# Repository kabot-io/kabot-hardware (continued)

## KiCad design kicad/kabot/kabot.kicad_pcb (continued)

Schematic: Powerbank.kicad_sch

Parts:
C1, C2, C7: 22u; C_1206_3216Metric; JLC C12891
L1: 1u; L_Changjiang_FNR5045S; JLC C436396
Q1: 2N7002K; SOT-23; JLC C8545
R3, R4: 1R; R_0603_1608Metric; JLC C22936
R5, R8, R10: 10k; R_0603_1608Metric; JLC C25804
R7: 5k1; R_0603_1608Metric; JLC C23186
U5: IP5306; Diodes_SO-8EP; JLC C181692

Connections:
/3V3: Q1.1 (G), R10.1; also elsewhere on the board
/+5V: U5.8 (VOUT); also elsewhere on the board
/BAT_V: R7.1, R8.1; also elsewhere on the board
/Powerbank LED/LED1+: U5.2 (LED1); also elsewhere on the board
/Powerbank LED/LED1-: U5.4 (LED3); also elsewhere on the board
/Powerbank LED/LED3+: U5.3 (LED2); also elsewhere on the board
/Powerbank/BAT+: C2.1, L1.2, R3.1, R7.2; also elsewhere on the board
/Powerbank/KEY_A: R5.2; also elsewhere on the board
/VBUS: R4.1, U5.1 (VIN); also elsewhere on the board
GND: C1.2, C2.2, C7.2, Q1.2 (S), R10.2, U5.9 (GND); also elsewhere on the board
unnamed: C7.1, R4.2
unnamed: Q1.3 (D), R8.2
unnamed: C1.1, R3.2, U5.6 (BAT)
unnamed: R5.1, U5.5 (KEY)
unnamed: L1.1, U5.7 (SW)

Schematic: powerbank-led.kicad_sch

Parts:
D13, D14, D15, D16: LED; LED_0603_1608Metric; JLC C2290
R9, R11, R12, R13: 5k1; R_0603_1608Metric; JLC C23186

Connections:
/Powerbank LED/LED1+: D13.2 (A), R11.2; also elsewhere on the board
/Powerbank LED/LED1-: D14.2 (A), D16.2 (A), R9.2, R12.2; also elsewhere on the board
/Powerbank LED/LED3+: D15.2 (A), R13.2; also elsewhere on the board
unnamed: D13.1 (K), R9.1
unnamed: D14.1 (K), R11.1
unnamed: D15.1 (K), R12.1
unnamed: D16.1 (K), R13.1

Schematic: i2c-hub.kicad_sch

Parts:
C37: 100n; C_0603_1608Metric; JLC C14663
U12: TCA9546APW; TSSOP-16_4.4x5mm_P0.65mm; JLC C42420613

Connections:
/3V3: C37.1, U12.16 (VCC); also elsewhere on the board
/SCL: U12.14 (SCL); also elsewhere on the board
/SDA: U12.15 (SDA); also elsewhere on the board
/Sensors/I2C Hub/SCL2: U12.10 (SC2)
/Sensors/I2C Hub/SCL3: U12.12 (SC3)
/Sensors/I2C Hub/SDA2: U12.9 (SD2)
/Sensors/I2C Hub/SDA3: U12.11 (SD3)
/Sensors/I2C Hub/~RESET: U12.3 (~RESET); also elsewhere on the board
/Sensors/SCL0: U12.5 (SC0); also elsewhere on the board
/Sensors/SCL1: U12.7 (SC1); also elsewhere on the board
/Sensors/SDA0: U12.4 (SD0); also elsewhere on the board
/Sensors/SDA1: U12.6 (SD1); also elsewhere on the board
GND: C37.2, U12.1 (A0), U12.2 (A1), U12.8 (GND), U12.13 (A2); also elsewhere on the board

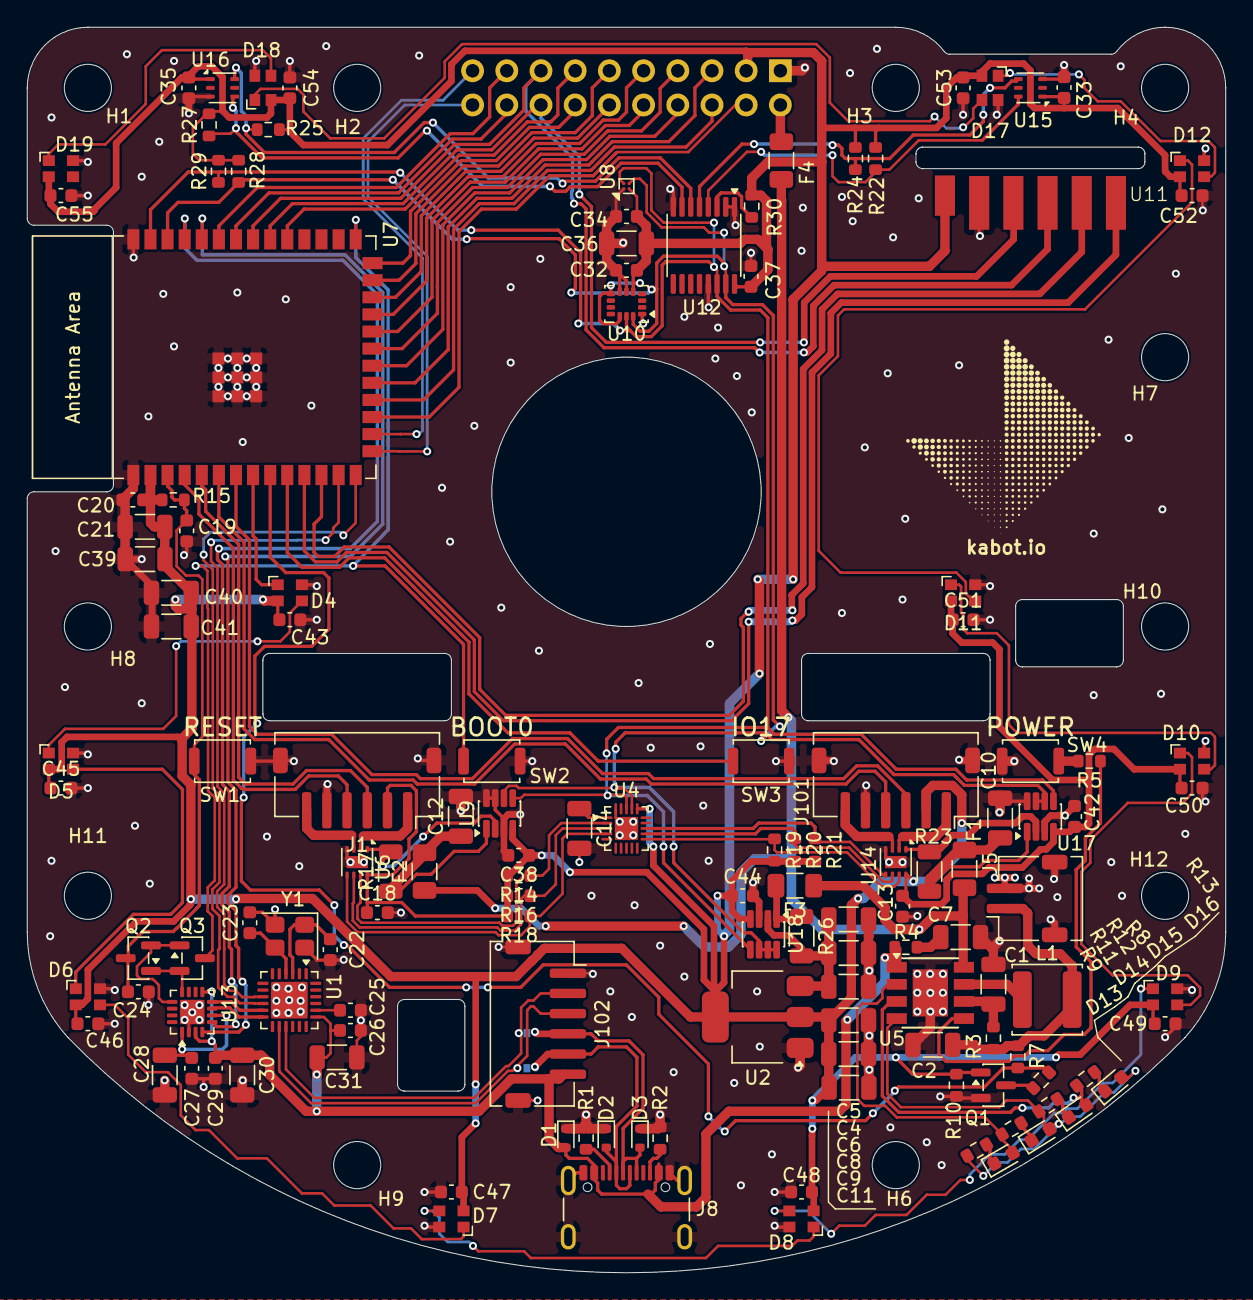
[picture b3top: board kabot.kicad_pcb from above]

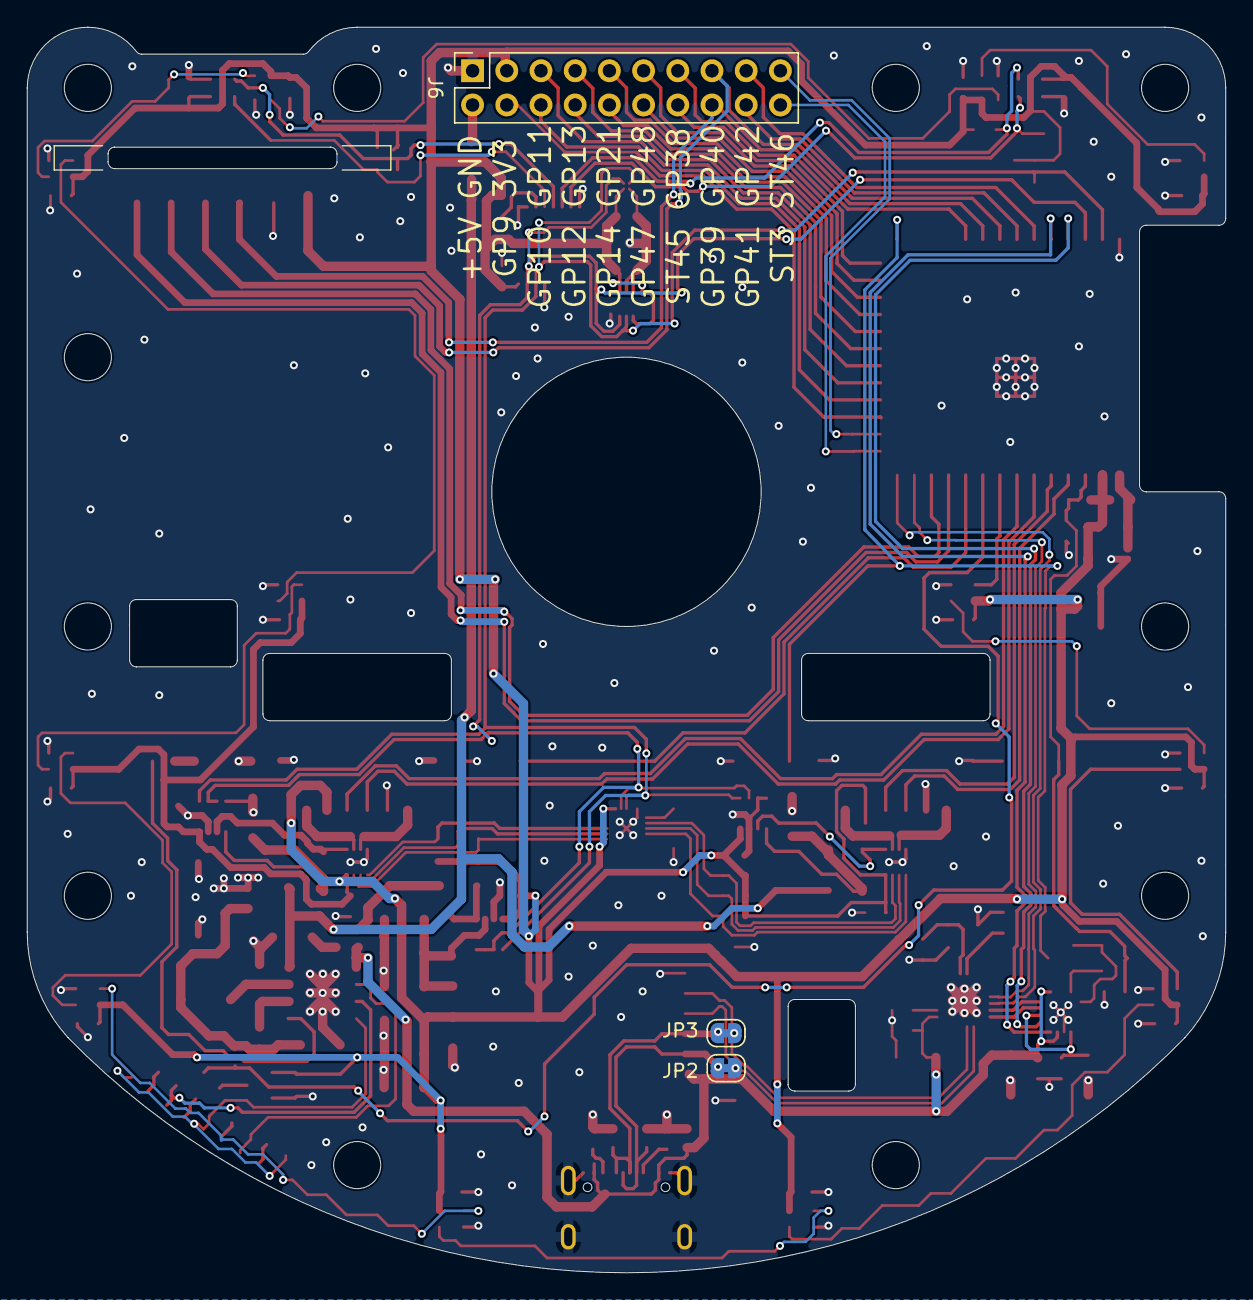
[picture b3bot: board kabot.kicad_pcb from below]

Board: 2 copper layers, 89.0 x 92.5 mm, 149 parts (3 on the bottom side), 100 nets.

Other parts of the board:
G1: LOGO; Logo
